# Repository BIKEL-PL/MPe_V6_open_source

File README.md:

# MPeV6 - DIY ebike computer

EN: More info https://bikel.pl/en/mpe-computer-for-e-bike/

PL: Więcej informacji: https://bikel.pl/komputer-mpe-do-e-bike/

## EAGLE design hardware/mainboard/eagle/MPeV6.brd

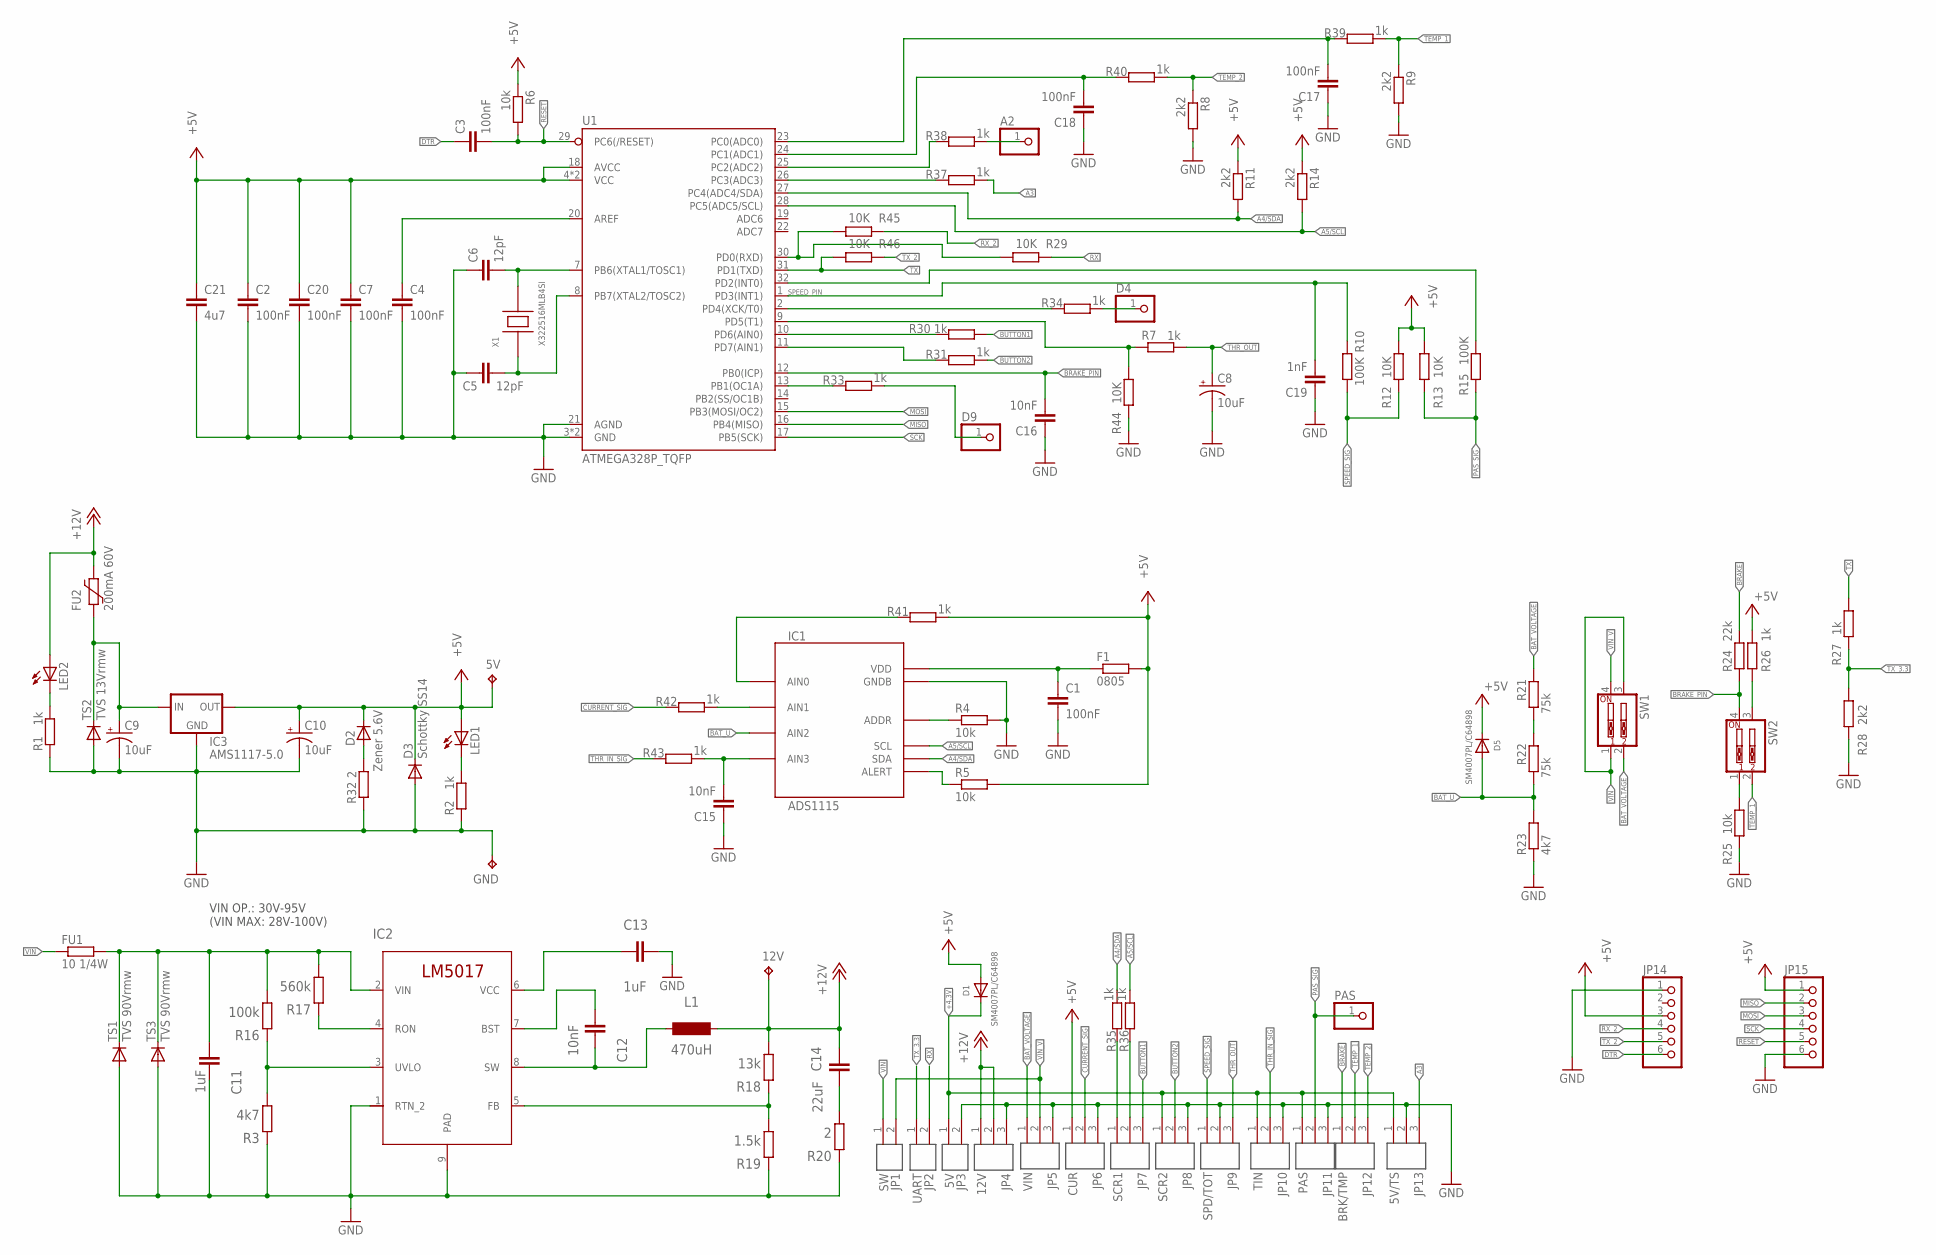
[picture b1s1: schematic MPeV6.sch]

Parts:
5V, 12V: TP_5V; P1-13
A2: PINHD-1X1; 1X01
C1, C2, C3, C4, C7, C17, C18, C20: 100nF; C0603
C5, C6: 12pF; C0603
C8, C9, C10: 10uF; EIA3216
C11: 1uF; C1206
C12: 10nF; C0805
C13: 1uF; C0603
C14: 22uF; C0805
C15, C16: 10nF; C0603
C19: 1nF; C0603
C21: 4u7; C0603
D1, D5: SM4007PL/C64898; SOD-123
D2: Zener 5.6V; MELF-MLL34
D3: Schottky SS14; DO-214AC
D4, D9: PINHD-1X1; 1X01
F1: 0805; R0805
FU1: 10 1/4W; 0204/7
FU2: 200mA 60V; 1812L
GND: TP_5V; P1-13
IC1: ADS1115; MSOP10_0.5
IC2: LM5017MR/NOPB; MRA08A
IC3: AMS1117-5.0; SOT223
JP1: SW; ARK254-PB+
JP2: UART; ARK254-2-COM
JP3: 5V; ARK254-2-5V
JP4: 12V; ARK254-3-12V-EL
JP5: VIN; ARK254-3-VIN
JP6: CUR; ARK254-3+S-
JP7: SCR1; ARK254-3
JP8: SCR2; ARK254-3
JP9: SPD/TOT; ARK254-3-SPD-TOT
JP10: TIN; ARK254-3+S-
JP11: PAS; ARK254-3+S-
JP12: BRK/TMP; ARK254-3-BRK-TMP
JP13: 5V/TS; ARK254-3-5V-TS
JP14, JP15: PINHD-1X6; 1X06
L1: 470uH; SLF12555T-102MR34-PF; LCSC C13738
LED1, LED2: LEDCHIP-LED0805; CHIP-LED0805
PAS: PINHD-1X1; 1X01
R1, R2, R7, R26, R27, R30, R31, R33, R34, R35, R36, R37, R38, R39, R40, R41, R42, R43: 1k; R0603
R3: 4k7; R0603
R4, R5, R6, R25: 10k; R0603
R8, R9, R11, R14, R28: 2k2; R0603
R10, R15: 100K; R0603
R12, R13, R29, R44, R45, R46: 10K; R0603
R16: 100k; R0603
R17: 560k; R0603
R18: 13k; R0603
R19: 1.5k; R0603
R20, R32: 2; R0805
R21, R22: 75k; R0805
R23: 4k7; R0805
R24: 22k; R0603
SW1, SW2: SW_DIP-2; EDG-02
TS1, TS3: TVS 90Vrmw; DO214AA
TS2: TVS 13Vrmw; DO214AA
U1: ATMEGA328P_TQFP; TQFP32-08
X1: X322516MLB4SI; IQG3225

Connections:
3: IC2.5 (FB), R18.2, R19.1
6: C13.2, IC2.6 (VCC)
7: IC2.4 (RON), R17.2
9: C14.2, R20.1
12V_FUSED: C9.+, FU2.2, IC3.3 (IN), TS2.C
+4.3V: D1.C, JP3.1, JP8.1, JP10.1, JP11.1, JP13.1
+5V: 5V.TP, C2.1, C7.1, C10.+, C20.1, C21.1, D1.A, D2.1 (C), D3.C, D5.C, F1.2, IC3.2 (OUT), IC3.4 (OUT), JP6.1, JP14.3, JP15.1, LED1.A, R5.2, R6.1, R11.1, R12.2, R13.2, R14.1, R26.2, R41.1, U1.4 (VCC), U1.6 (VCC), U1.18 (AVCC)
+12V: 12V.TP, C14.1, FU2.1, JP4.1, JP4.2, L1.P$2 (2), LED2.A, R18.1
A2: R38.2, U1.25 (PC2(ADC2))
A3: JP13.3, R37.1
A4/SDA: IC1.9 (SDA), R11.2, R35.1, U1.27 (PC4(ADC4/SDA))
A5/SCL: IC1.10 (SCL), R14.2, R36.1, U1.28 (PC5(ADC5/SCL))
BAT_U: D5.A, IC1.6 (AIN2), R22.1, R23.2
BAT_VOLTAGE: JP5.1, R21.2, SW1.2
BRAKE: JP12.1, R24.2
BRAKE_PIN: C16.2, R24.1, SW2.4, U1.12 (PB0(ICP))
BUTTON1: JP7.3, R30.1
BUTTON2: JP8.2, R31.1
CSIG: IC1.5 (AIN1), R42.1
CURRENT_SIG: JP6.2, R42.2
DTR: C3.1, JP14.6
GND: C1.2, C2.2, C4.2, C5.1, C6.1, C7.2, C8.-, C9.-, C10.-, C11.2, C13.1, C15.1, C16.1, C17.1, C18.1, C19.1, C20.2, C21.2, D3.A, GND.TP, IC1.3 (GNDB), IC2.1 (RTN_2), IC2.9 (PAD), IC3.1 (GND), JP3.2, JP4.3, JP5.3, JP6.3, JP8.3, JP9.2, JP10.3, JP11.3, JP13.2, JP14.1, JP15.6, R1.1, R2.1, R3.2, R4.2, R8.2, R9.2, R19.2, R20.2, R23.1, R25.1, R28.1, R32.1, R44.1, TS1.A, TS2.A, TS3.A, U1.3 (GND), U1.5 (GND), U1.21 (AGND)
MISO: JP15.2, U1.16 (PB4(MISO))
MOSI: JP15.3, U1.15 (PB3(MOSI/OC2))
unnamed: LED1.C, R2.2
unnamed: JP7.1, R35.2
unnamed: IC2.3 (UVLO), R3.1, R16.2
unnamed: JP7.2, R36.2
unnamed: D9.1, R33.1
unnamed: C12.1, IC2.7 (BST)
unnamed: R7.1, R44.2, U1.9 (PD5(T1))
unnamed: C4.1, U1.20 (AREF)
unnamed: LED2.C, R1.2
unnamed: R15.2, U1.32 (PD2(INT0))
unnamed: IC1.1 (ADDR), R4.1
unnamed: IC1.2 (ALERT), R5.1
unnamed: D4.1, R34.1
unnamed: IC1.4 (AIN0), R41.2
unnamed: R29.2, R45.2, U1.30 (PD0(RXD))
unnamed: D2.2 (A), R32.2
unnamed: R25.2, SW2.1
unnamed: R30.2, U1.10 (PD6(AIN0))
unnamed: R31.2, U1.11 (PD7(AIN1))
unnamed: R26.1, SW2.3
unnamed: C11.1, FU1.2, IC2.2 (VIN), R16.1, R17.1, TS1.C, TS3.C
unnamed: R33.2, U1.13 (PB1(OC1A))
unnamed: R34.2, U1.2 (PD4(XCK/T0))
unnamed: C6.2, U1.7 (PB6(XTAL1/TOSC1)), X1.3 (PIN2)
unnamed: C5.2, U1.8 (PB7(XTAL2/TOSC2)), X1.1 (PIN1)
unnamed: R21.1, R22.2
unnamed: R37.2, U1.26 (PC3(ADC3))
unnamed: A2.1, R38.1
PAS_SIG: JP11.2, PAS.1, R13.1, R15.1
RESET: C3.2, JP15.5, R6.2, U1.29 (PC6(/RESET))
RX: JP2.2, R29.1
RX_2: JP14.4, R45.1
SCK: JP15.4, U1.17 (PB5(SCK))
SPEED_PIN: C19.2, R10.2, U1.1 (PD3(INT1))
SPEED_SIG: JP9.1, R10.1, R12.1
SW: C12.2, IC2.8 (SW), L1.P$1 (1)
T1: C17.2, R39.2, U1.23 (PC0(ADC0))
T2: C18.2, R40.2, U1.24 (PC1(ADC1))
TEMP_1: JP12.2, R9.1, R39.1, SW2.2
TEMP_2: JP12.3, R8.1, R40.1
THR_IN_SIG: JP10.2, R43.2
THR_OUT: C8.+, JP9.3, R7.2
TSIG: C15.2, IC1.7 (AIN3), R43.1
TX: R27.2, R46.2, U1.31 (PD1(TXD))
TX_2: JP14.5, R46.1
TX_3.3: JP2.1, R27.1, R28.2
VDD: C1.1, F1.1, IC1.8 (VDD)
VIN: FU1.1, JP1.1, SW1.1, SW1.3
VIN_V: JP1.2, JP5.2, SW1.4

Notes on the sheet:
VIN OP.: 30V-95V (VIN MAX: 28V-100V)

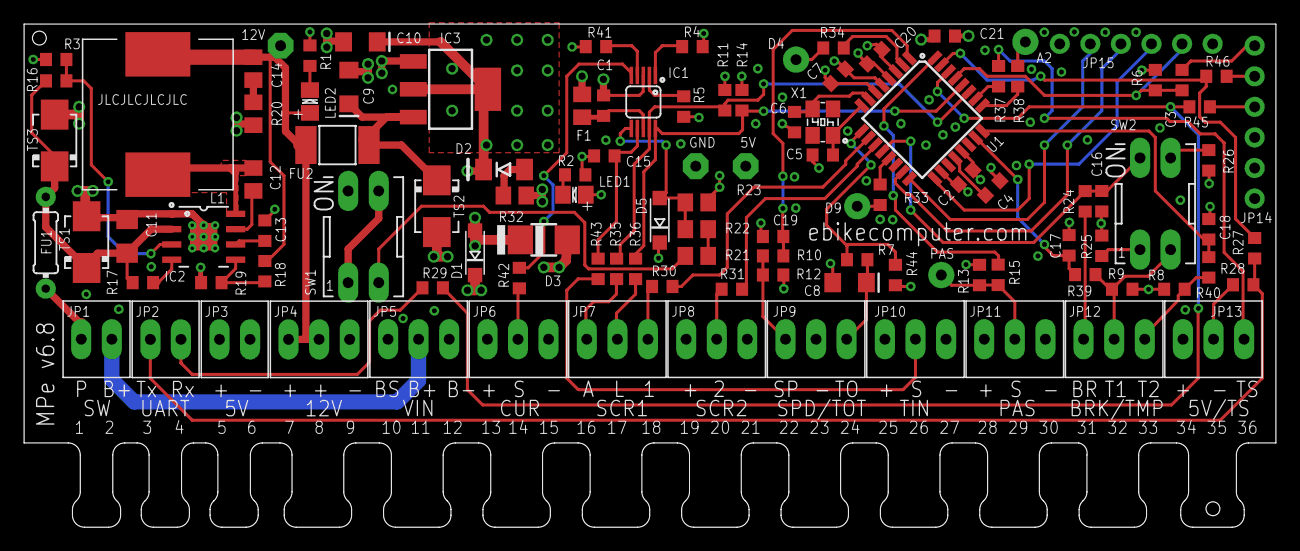
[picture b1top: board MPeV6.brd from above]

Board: 4 copper layers, 104.0 x 41.8 mm, 109 parts (0 on the bottom side), 73 nets.

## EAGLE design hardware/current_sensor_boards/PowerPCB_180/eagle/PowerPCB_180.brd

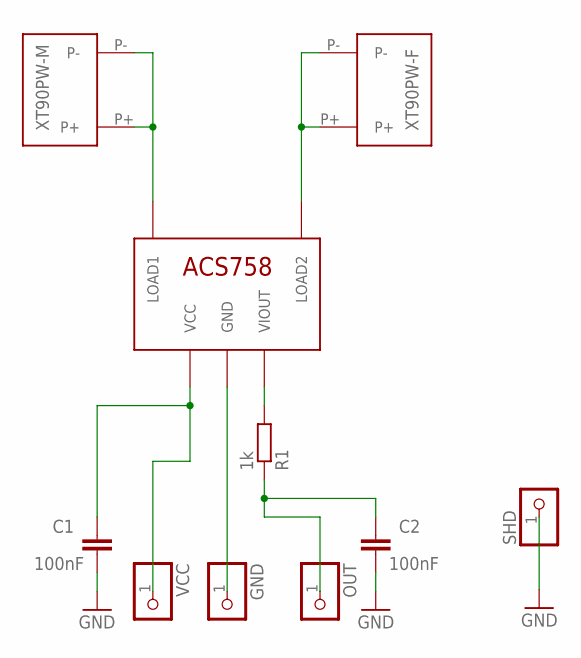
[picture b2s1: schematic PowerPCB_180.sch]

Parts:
ACS758_1: ACS758; ACS758-PFF
C1, C2: 100nF; C0805
GND: PINHD-1X1; 1X01
OUT: PINHD-1X1; 1X01
R1: 1k; R0805
SHD: PINHD-1X1; 1X01
VCC: PINHD-1X1; 1X01
XT90PW-F1: XT90PW-F
XT90PW-M1: XT90PW-M

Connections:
GND: ACS758_1.GND, C1.2, C2.2, GND.1, SHD.1
unnamed: ACS758_1.VIOUT, R1.2
unnamed: C2.1, OUT.1, R1.1
unnamed: ACS758_1.LOAD1, XT90PW-M1.P+, XT90PW-M1.P-
unnamed: ACS758_1.LOAD2, XT90PW-F1.P+, XT90PW-F1.P-
unnamed: ACS758_1.VCC, C1.1, VCC.1

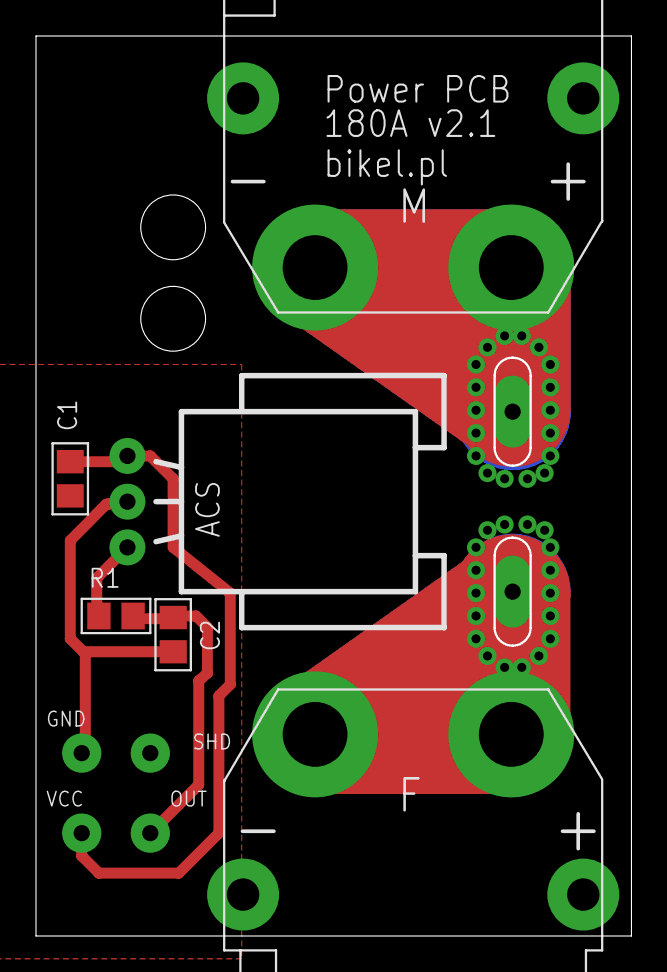
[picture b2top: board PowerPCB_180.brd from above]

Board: 2 copper layers, 33.0 x 49.9 mm, 10 parts (0 on the bottom side), 6 nets.

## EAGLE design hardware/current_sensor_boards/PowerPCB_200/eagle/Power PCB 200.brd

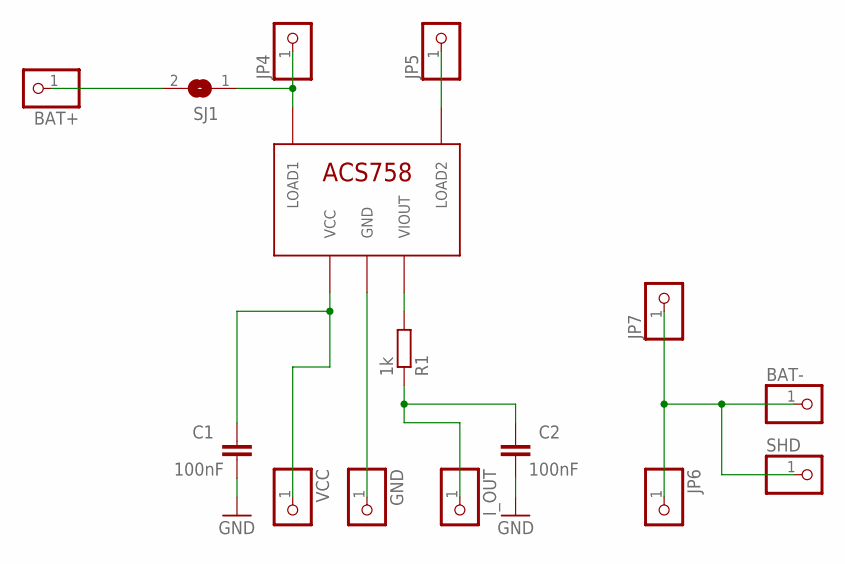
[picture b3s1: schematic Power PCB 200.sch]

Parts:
ACS758_1: ACS758; ACS758-PFF
BAT+: PINHD-1X1; 1X01
BAT-: PINHD-1X1; 1X01
C1, C2: 100nF; C0805
GND: PINHD-1X1; 1X01
I_OUT: PINHD-1X1; 1X01
JP4, JP5, JP6, JP7: PINHD-1X1; 1X01
R1: 1k; R0805
SHD: PINHD-1X1; 1X01
SJ1: SJ
VCC: PINHD-1X1; 1X01

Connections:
BAT-: BAT-.1, JP6.1, JP7.1, SHD.1
GND: ACS758_1.GND, C1.2, C2.2, GND.1
unnamed: ACS758_1.VIOUT, R1.2
unnamed: C2.1, I_OUT.1, R1.1
unnamed: ACS758_1.LOAD1, JP4.1, SJ1.1
unnamed: ACS758_1.LOAD2, JP5.1
unnamed: BAT+.1, SJ1.2
unnamed: ACS758_1.VCC, C1.1, VCC.1

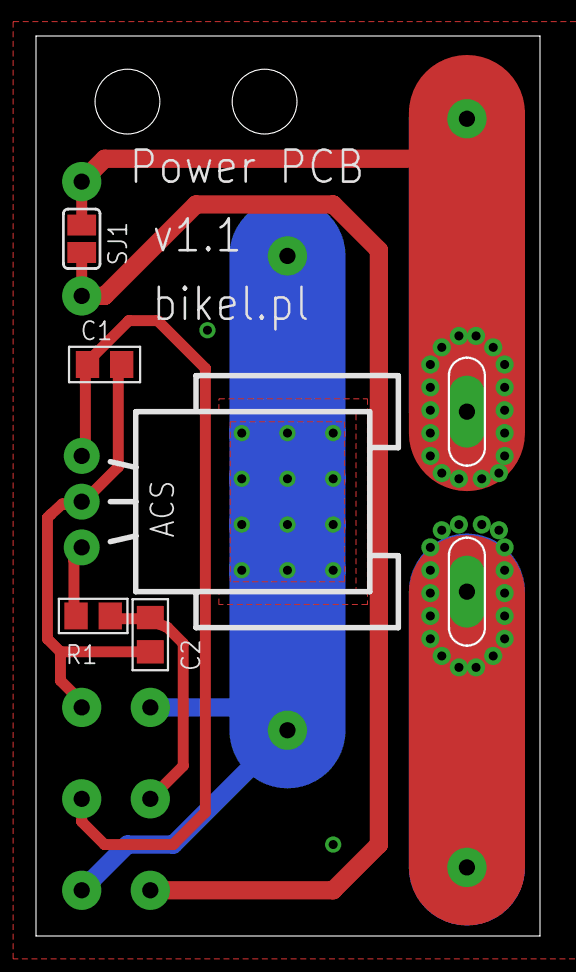
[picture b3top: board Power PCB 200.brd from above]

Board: 2 copper layers, 27.9 x 49.9 mm, 15 parts (0 on the bottom side), 8 nets.

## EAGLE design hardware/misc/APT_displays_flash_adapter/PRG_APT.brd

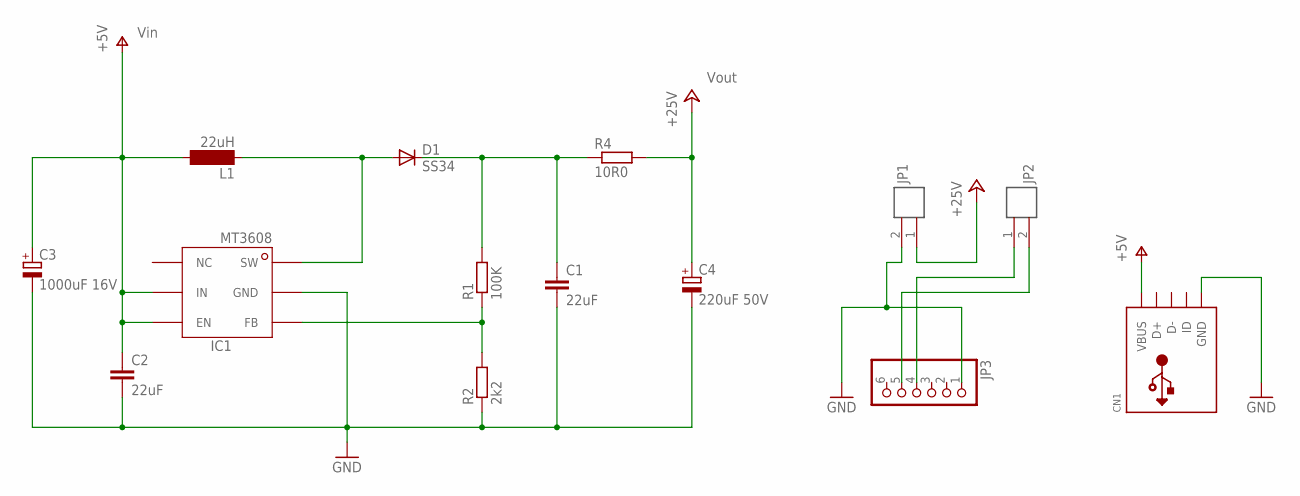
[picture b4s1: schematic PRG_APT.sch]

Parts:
C1, C2: 22uF; C0805
C3: 1000uF 16V; 153CLV-0810
C4: 220uF 50V; 153CLV-1010
CN1: USBMINIB; USB-MINIB
D1: SS34; DO-214AC
IC1: MT3608SOT23-6; SOT23-6
JP1, JP2: ARK254-2
JP3: PINHD-1X6; 1X06
L1: 22uH; SLF12555T-102MR34-PF
R1: 100K; R0805
R2: 2k2; R0805
R4: 10R0; M1206

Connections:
+25V: C4.+, JP1.1, R4.2
GND: C1.2, C2.2, C3.-, C4.-, CN1.GND, IC1.P$2 (GND), JP1.2, JP3.1, R2.1
unnamed: D1.A, IC1.P$1 (SW), L1.P$1 (1)
unnamed: IC1.P$3 (FB), R1.1, R2.2
unnamed: JP2.1, JP3.4
unnamed: JP2.2, JP3.5
unnamed: C1.1, D1.C, R1.2, R4.1
V+: C2.1, C3.+, CN1.VBUS, IC1.P$4 (EN), IC1.P$5 (IN), L1.P$2 (2)

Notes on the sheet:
Vin
Vout

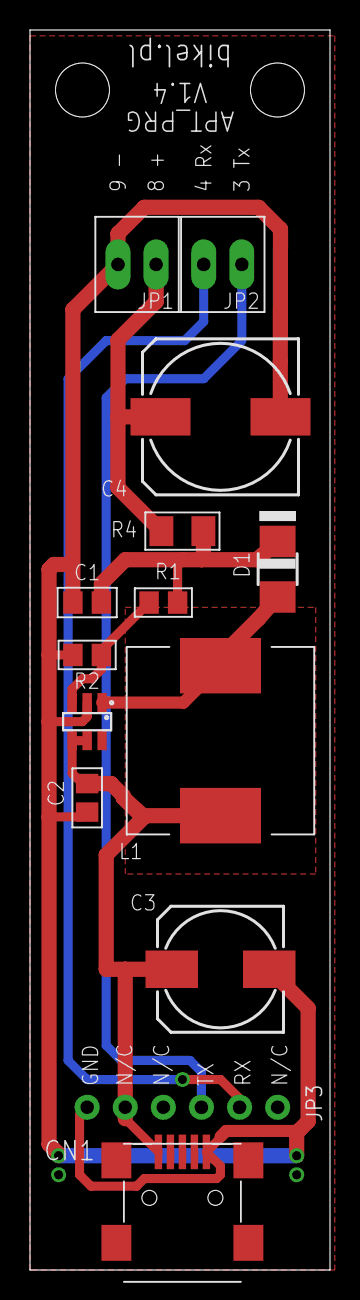
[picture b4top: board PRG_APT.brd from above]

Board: 2 copper layers, 20.0 x 82.7 mm, 14 parts (0 on the bottom side), 8 nets.

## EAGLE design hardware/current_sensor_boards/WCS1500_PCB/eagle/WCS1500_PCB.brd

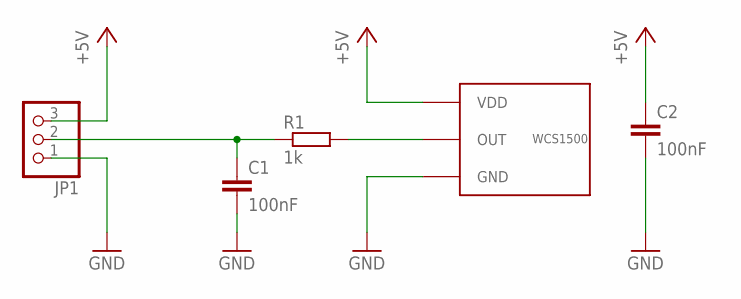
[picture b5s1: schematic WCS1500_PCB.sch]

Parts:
C1, C2: 100nF; C0603
JP1: PINHD-1X3; 1X03
R1: 1k; R0603
U$1: WCS1500

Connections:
+5V: C2.1, JP1.3, U$1.VDD
GND: C1.2, C2.2, JP1.1, U$1.GND
unnamed: R1.2, U$1.OUT
unnamed: C1.1, JP1.2, R1.1

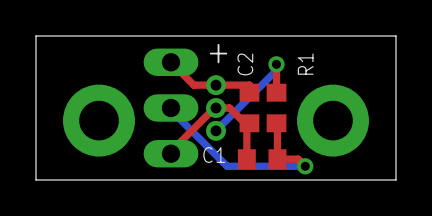
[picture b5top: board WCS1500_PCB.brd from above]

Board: 2 copper layers, 20.0 x 8.0 mm, 5 parts (0 on the bottom side), 4 nets.

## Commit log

2025-05-25 Add files
2025-05-25 Add readme
2025-05-25 Add maxicolor readme
2025-05-25 Add smartphone app readme

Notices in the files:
parts and their libraries:
SparkFun-IC-Microcontroller: Licensing: Creative Commons ShareAlike 4.0 International - https://creativecommons.org/licenses/by-sa/4.0
lm1117: (c) 2014 Samuel Lourenço
